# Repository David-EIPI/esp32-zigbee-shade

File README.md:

# esp32-zigbee-shade

## Overview

This external window shade is designed to shield the room from sunlight, reducing the load on the air conditioner. I upgraded a basic corded roller shade by integrating a small DC motor and a Zigbee controller compatible with my Home Assistant network.

## Firmware

The firmware is written in C and built using `idf.py`.
It exposes 2 endpoints with 3 clusters:

* **Window covering** (shade control)
* **OTA** (remote firmware upgrade)
* **Temperature measurement** (on-chip temperature sensor)

The temperature sensor reports via Zigbee to monitor the temperature inside the control box, as summer ambient temperatures often exceed 35°C, and the enclosure tightly houses both the ESP32 and the motor driver.

See [here](https://github.com/David-EIPI/esp32-zigbee-light/blob/main/BUILD.md) instructions on building the firmware using `idf.py` on Linux.

## Hardware

### Mechanical

This window cover is based on the VICLLAX 5×6 ft corded roll-up shade, which uses an aluminum tube with a 1 1/8" (28 mm) inner diameter.

Several inexpensive DC motors with pre-assembled gearheads are available online, commonly found as clones of the Bringsmart High Torque Worm Gear DC motor. Most of these motors use gearheads with D-shaped shafts, predominantly 8 mm but occasionally 6 mm.

These motors and gearboxes come in various voltages and torque ratings. I used a 12 V motor equipped with a 200× ratio gearbox rated for 4 kg·cm torque. This choice turned out to be excessive, as a gearbox with a 60× or 80× ratio would have been sufficient.

To couple the motor to the roller tube, I repurposed Zemismart’s replacement 28 mm nylon gears, removing one tooth from each side and filing the D-shaped channel to match the motor shaft.

\
*The original gear compared to the modified gear (two teeth removed, D-shape filed).*

\
*Gear mounted on the motor shaft.*

\
*Gear inserted into the shade tube.*

For motor mounting, I modified the original bracket supplied with the shade. I broke off the support lip, drilled two additional holes, and added a countersunk hole at the existing cut. The modified bracket is shown below:

The image below shows the fully assembled motor with the coupling gear:

### Electronics

The control system uses an ESP32-H2 chip on Tenstar’s Supermini board (or a clone). [This board sometimes exhibits startup issues](https://github.com/David-EIPI/esp32-zigbee-light) when powered from a standalone DC-DC converter. Although the board already has an RC circuit on its reset line, it is apparently insufficient, as intermittent boot failures occur on power-up. I resolved this issue by soldering an additional 0.22 µF capacitor in parallel with the existing one.

The ESP32-H2 Supermini clones available on Aliexpress vary. The most notable difference is component placement: some boards have all components mounted on the top side, while other (usually cheaper) versions have components on both sides. For the double-sided boards, the additional capacitor should be soldered on the bottom side, as shown in the photo. Although I only had 0603-sized capacitors at hand, it fit comfortably next to the existing one.

Due to bottom-side components, the ESP32-H2 board must be mounted above the mainboard:

The motor driver uses a DRV8871 chip from Texas Instruments. It accepts a PWM control signal, easily generated using the standard ESP32 `ledc` controller.

The motor features a rotary encoder interfaced to the ESP32’s standard pulse-counter controller. This encoder maintains consistent upper and lower travel limits and allows precise partially-open positioning of the shade.

A notable drawback of this motor is its hardwired, non-weatherproof cable. Its durability in summer humidity remains uncertain, and some corrosion is likely inevitable. To minimize electrochemical corrosion, I designed the control circuit to disconnect power from the motor and encoder when the shade is stationary.

The final assembly fits neatly into the Serpac 110i BK enclosure. I only needed to cut openings for the 6-pin motor connector (on the left) and the power jack (on the right):

Since the motor connector is not polarized it may be a good idea to mark the connector orientation on the enclosure side.

## ZHA quirk

Although ZHA supports window coverings, additional configuration using a quirk is required. The quirk provides coverage percentage display, lift velocity settings, and essential calibration buttons for setting upper and lower limits.

The screenshot below shows the device page (quirk applied):

Calibration of limits must be completed before using the shade for the first time. The calibration procedure is as follows:

* Press "↓" to start lowering the shade, stopping roughly halfway.
  This step isn't strictly required, but it reduces the likelihood of pulse counter overflow, as the pulse counter range is limited to 16 bits.
* Press "reset limits".
* Press "↑" to raise the shade, stopping at the desired upper position. Then press "Set upper limit" to record this position.
* Press "↓" again, stopping at the desired lower position. Then press "Set lower limit" to record this position.

Depending on Zigbee network topology, commands may take about a second to process. Thus, if the motor rolls quickly, reducing the lift velocity before calibration may improve accuracy.

## Over-the-air (OTA) upgrade

The firmware supports OTA upgrades. ESP's Zigbee library handles most tasks, leaving only four essential `esp_ota_*` function calls (`begin`, `data`, `write`, and `end`) for firmware implementation, aside from cluster allocation and error checking. The SDK provides an image builder tool (`image_builder_tool.py`) to convert compiled firmware into OTA format (see the `ota_image.sh` script for a usage example).

On the Home Assistant side, the Zigpy configuration should be added to `configuration.yaml` under the `zha:` section, as illustrated below:

```
zha:
  zigpy_config:
    ota:
      extra_providers:
        - type: zigpy_local
          index_file: /config/zha_ota/local_index.json
        - type: advanced
          warning: I understand I can *destroy* my devices by enabling OTA
              updates from files. Some OTA updates can be mistakenly applied to the
              wrong device, breaking it. I am consciously using this at my own risk.
          path: /config/zha_ota
```

OTA update files (JSON and BIN) should be uploaded to the specified directory (`/config/zha_ota` in this example). When using the JSON OTA provider, Home Assistant will display firmware version and release notes from the provided JSON file.

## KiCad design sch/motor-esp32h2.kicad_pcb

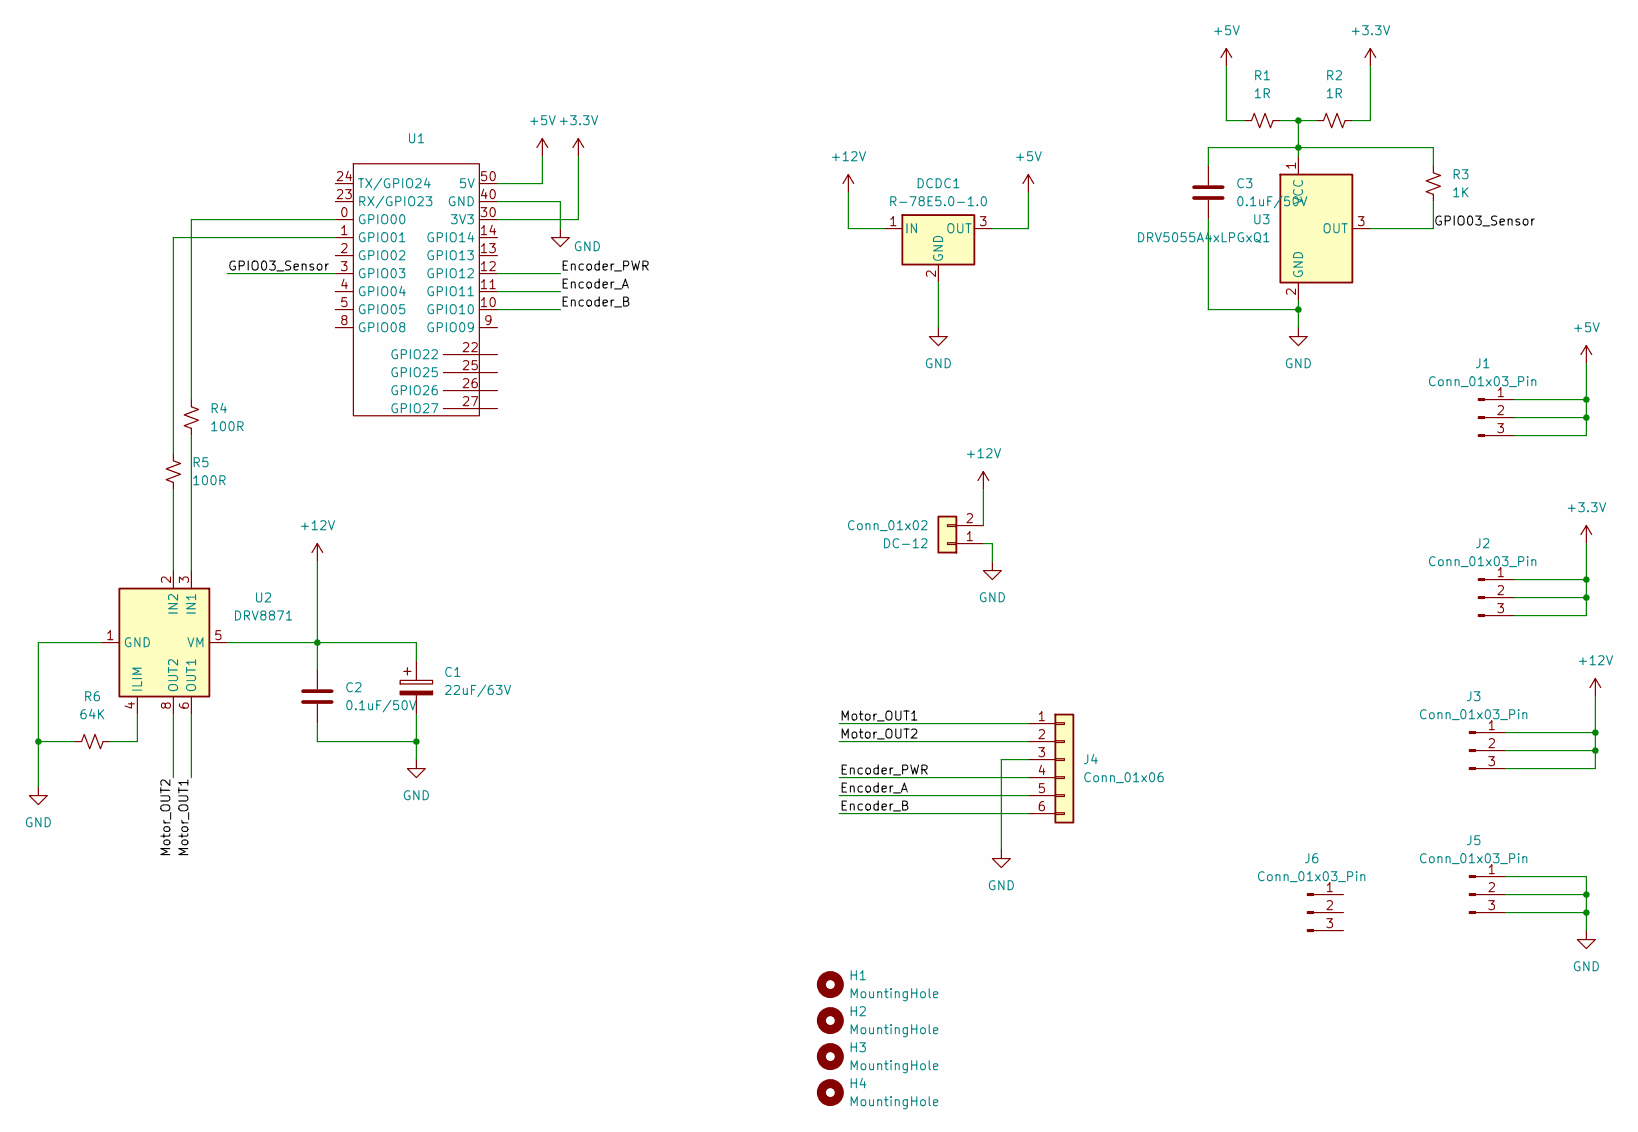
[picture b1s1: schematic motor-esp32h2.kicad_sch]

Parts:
C1: 22uF/63V; CP_Radial_D6.3mm_P2.50mm
C2, C3: 0.1uF/50V; C_0603_1608Metric_Pad1.08x0.95mm_HandSolder
DC-12: Conn_01x02; TE_826576-2_1x02_P3.96mm_Vertical
DCDC1: R-78E5.0-1.0; Converter_DCDC_RECOM_R-78E-0.5_THT
H1, H2, H3, H4: MountingHole; MountingHole_2.7mm_M2.5
J1, J2, J3, J5, J6: Conn_01x03_Pin; PinHeader_1x03_P2.54mm_Vertical
J4: Conn_01x06; PinHeader_1x06_P2.54mm_Vertical
R1, R2: 1R; R_0603_1608Metric_Pad0.98x0.95mm_HandSolder
R3: 1K; R_0603_1608Metric_Pad0.98x0.95mm_HandSolder
R4, R5: 100R; R_0603_1608Metric_Pad0.98x0.95mm_HandSolder
R6: 64K; R_0603_1608Metric_Pad0.98x0.95mm_HandSolder
U1: ESP32-H2-SuperMini
U2: DRV8871; Texas_HTSOP-8-1EP_3.9x4.9mm_P1.27mm_EP2.95x4.9mm_Mask2.4x3.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
U3: DRV5055A4xLPGxQ1; TO-92_Inline

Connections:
+3.3V: J2.1, J2.2, J2.3, R2.2, U1.30 (3V3)
+5V: DCDC1.3 (OUT), J1.1, J1.2, J1.3, R1.1, U1.50 (5V)
+12V: C1.1, C2.1, DC-12.2, DCDC1.1 (IN), J3.1, J3.2, J3.3, U2.5 (VM)
/Encoder_A: J4.5, U1.11 (GPIO11)
/Encoder_B: J4.6, U1.10 (GPIO10)
/Encoder_PWR: J4.4, U1.12 (GPIO12)
/GPIO03_Sensor: R3.1, U1.3 (GPIO03), U3.3 (OUT)
/Motor_OUT1: J4.1, U2.6 (OUT1)
/Motor_OUT2: J4.2, U2.8 (OUT2)
GND: C1.2, C2.2, C3.2, DC-12.1, DCDC1.2 (GND), J4.3, J5.1, J5.2, J5.3, R6.1, U1.40 (GND), U2.1 (GND), U2.7 (GND), U2.9 (GND), U3.2 (GND)
unnamed: R4.1, U1.0 (GPIO00)
unnamed: R5.1, U1.1 (GPIO01)
unnamed: R6.2, U2.4 (ILIM)
unnamed: R4.2, U2.3 (IN1)
unnamed: R5.2, U2.2 (IN2)
unnamed: C3.1, R1.2, R2.1, R3.2, U3.1 (VCC)

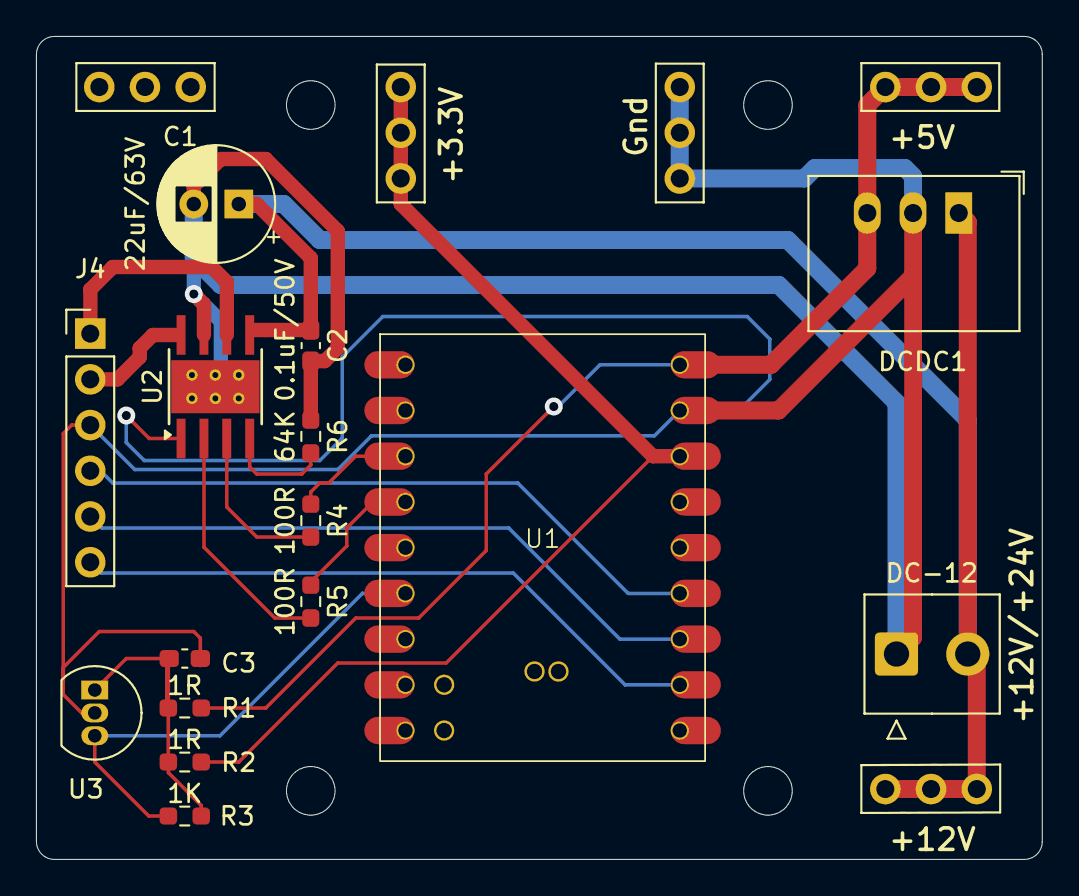
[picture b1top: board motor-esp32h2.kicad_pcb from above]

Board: 2 copper layers, 55.9 x 45.7 mm, 24 parts (0 on the bottom side), 16 nets.

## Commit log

2025-07-03 Initial upload.
2025-07-08 Move source files to a separate folder for cleaner directory structure.
2025-07-29 Remove factory partition, increase size of the OTA partitions.
2025-07-29 Change pinout to match the update mainboard.
2025-07-29 Change firmware version to prevent accidental update of the old boards with different encoder connection.
2025-07-29 Correct the typo that throws compilation error.
2025-07-29 Add more details about the controller.
2025-07-29 Add the image files and move cmakelist.txt to the correct subfolders.
2025-07-29 Add link to the firmware build instructions.
2025-07-29 Track project dependencies
2025-07-29 Fix the link to the build instructions
2025-07-30 Cleanup the unused code, add lic headers to the files.
2025-07-31 Add extra checks to up/down commands to avoid possible small moves in a wrong direction.
2025-07-31 Also update the OTA version
